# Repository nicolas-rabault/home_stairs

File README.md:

# My home stairs overkill automation project

I create this to make my stairs awesome.
Watch the video :

This project contain everything allowing you to create your own overkill led animated stairs at home.
This project use :

 - [Kicad](https://www.kicad.org/) for the hardware design
 - [Platformio](https://platformio.org/) as IDE
 - [Luos](https://www.luos.io/) as embedded software architecture
 - [CubeMX](https://www.st.com/en/development-tools/stm32cubemx.html) to generate MCU low level interfaces

## How to open the electronic design :electric_plug:
Electronics have been based on [Luos example electronic design](https://github.com/Luos-io/Examples/tree/master/Hardware) except for [the fuel gauge shield](/hardware/l0-shield/l0_load). You can open and modify all of them using Kicad. This design use Luos_components library for more information to install and use it read [Luos doc](https://docs.luos.io).

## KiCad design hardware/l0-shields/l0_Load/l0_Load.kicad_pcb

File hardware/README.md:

[](
https://github.com/Luos-io/Examples/blob/master/LICENSE)

# Electronics basis

This folder contains customized hardware boards from luos examples repository : https://github.com/Luos-io/Examples
 - **l0-shields**: Different shields that can be used directly on the Luos L0 board for added functionality.
 - **00_Common_Libraries**: a set of Kicad libraries commonly used.

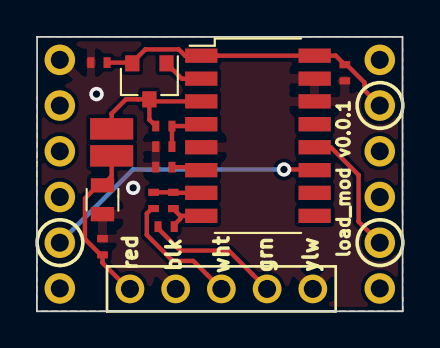
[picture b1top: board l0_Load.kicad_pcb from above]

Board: 2 copper layers, 20.3 x 15.2 mm, 15 parts (0 on the bottom side), 13 nets.

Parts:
C1, C3, C4, C5, C6: 0.1uf; R_0402_NoSilk
C2: 10uf; R_0805
J1: Header5Contacts; 826926-5
J2: l0_Shield_Socket
L1: 3.3uh; 1008
Q1: Q_NPN_BEC; SOT-23
R1: 20K; R_0402_NoSilk
R2: 8.2K; R_0402_NoSilk
R3, R4: 100; R_0402_NoSilk
U1: HX711; SOP-16_4.4x10.4mm_Pitch1.27mm

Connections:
+3V3: C5.1, C6.1, J2.5, Q1.2, U1.1, U1.16
/A+: J1.4, R4.1
/A-: J1.3, R3.1
/DAT: J2.2, U1.12
/SCK: J2.11, U1.11
GND: C1.2, C2.2, C3.1, C5.2, C6.2, J1.2, J1.5, J2.7, R2.2, U1.5, U1.14, U1.15
unnamed: C1.1, C2.1, J1.1, L1.1
unnamed: C3.2, U1.6
unnamed: C4.1, R3.2, U1.7
unnamed: C4.2, R4.2, U1.8
unnamed: L1.2, Q1.3, R1.1, U1.3
unnamed: Q1.1, U1.2
unnamed: R1.2, R2.1, U1.4

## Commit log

2021-12-21 working first prototype
2022-01-18 First working revision
2022-01-19 Add a bootloader compatible binary compilation
2022-01-26 Add master configurations
2022-01-26 Add a script allowing to build and flash the entire product
2022-01-28 update RTB filtering
2022-01-28 remove warning
2022-01-28 Fix slot map computation
2022-01-28 Avoid color overflow
2022-01-28 Turn of led strip at detection
2022-01-28 size the led_strip buffer
2022-01-28 Update led Strip buffer only in case of color changes
2022-01-28 Re-enable the StepMngr app
2022-01-28 Increase the MAX_RTB_ENTRY to be able to support 11 steps.
2022-05-11 Switch to Luos engine 2.4.0
2022-05-11 Fix 1 color receiving management
2022-05-11 Fix a buffer overflow
2022-05-11 Secure messages transmition
2022-05-11 delta_intensity become light_intensity it's now unsigned and secured
2022-05-11 Add some security into led strip reception
2022-05-11 Frames are now uint8_t matrix
2022-05-11 Increase buffer sizes
2022-05-19 secure it
2022-06-02 Change wave speed
2022-09-24 Light intensity auto-scaling
2022-09-24 migrate to 2.6.2
2022-09-24 Hide a bug
2022-10-01 generate a wave at boot coming from master
2022-10-01 Fix miss initialization of values generation random light scaling.
2022-10-01 Increase timing for detection and bug hide
2022-10-01 Secure end detection reception to be sure to be detected before running.
2022-10-01 Do not tare after detection, it take too long.
2022-10-01 fix systick function call mistake
2022-10-01 Clean detection process allowing to run Luos_loop properly
2022-10-01 Go back to bootloader in case of hardfault
2022-10-01 Fix bootloader configuration
2022-10-01 Tare the sensor at init avoiding a glitch after detection.
2022-10-02 remove useless tare at detection
2022-10-02 Auto select sensor direction
2022-10-02 Allow to stop frames display
2022-10-02 fix offset
2022-10-02 Add a monitoring mode in case of Gate : - Take back control of the sensor - Send back filtered sensor values and light intensity
2022-10-02 Add an offset on the light intensity calculation to avoid noise.
2022-10-02 fix master wave
2022-10-02 Fix bootloader argument.
2022-10-04 Increase gain and offset to get better liminance and noise avoidance
2022-10-04 Remove useless sensor direction due to absolute calculations
2022-10-04 Reset gain when no detection occure allowing to maximize light intensity in any condition
2022-10-04 Add some comment to make it easier to read.
2022-10-04 Add a bootloader reset command before flashing avoiding heavy routing table.
2022-10-04 Improve bug hide...
2022-10-19 Add color management
